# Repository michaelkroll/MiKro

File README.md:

MiKro
==========

The Arduino UNO form factor based MiKro which is using an ATmega 1284p uC from Atmel
Details see on Michael Kroll's Blog at http://www.mkroll.mobi/?page_id=1696
 
Photos
===

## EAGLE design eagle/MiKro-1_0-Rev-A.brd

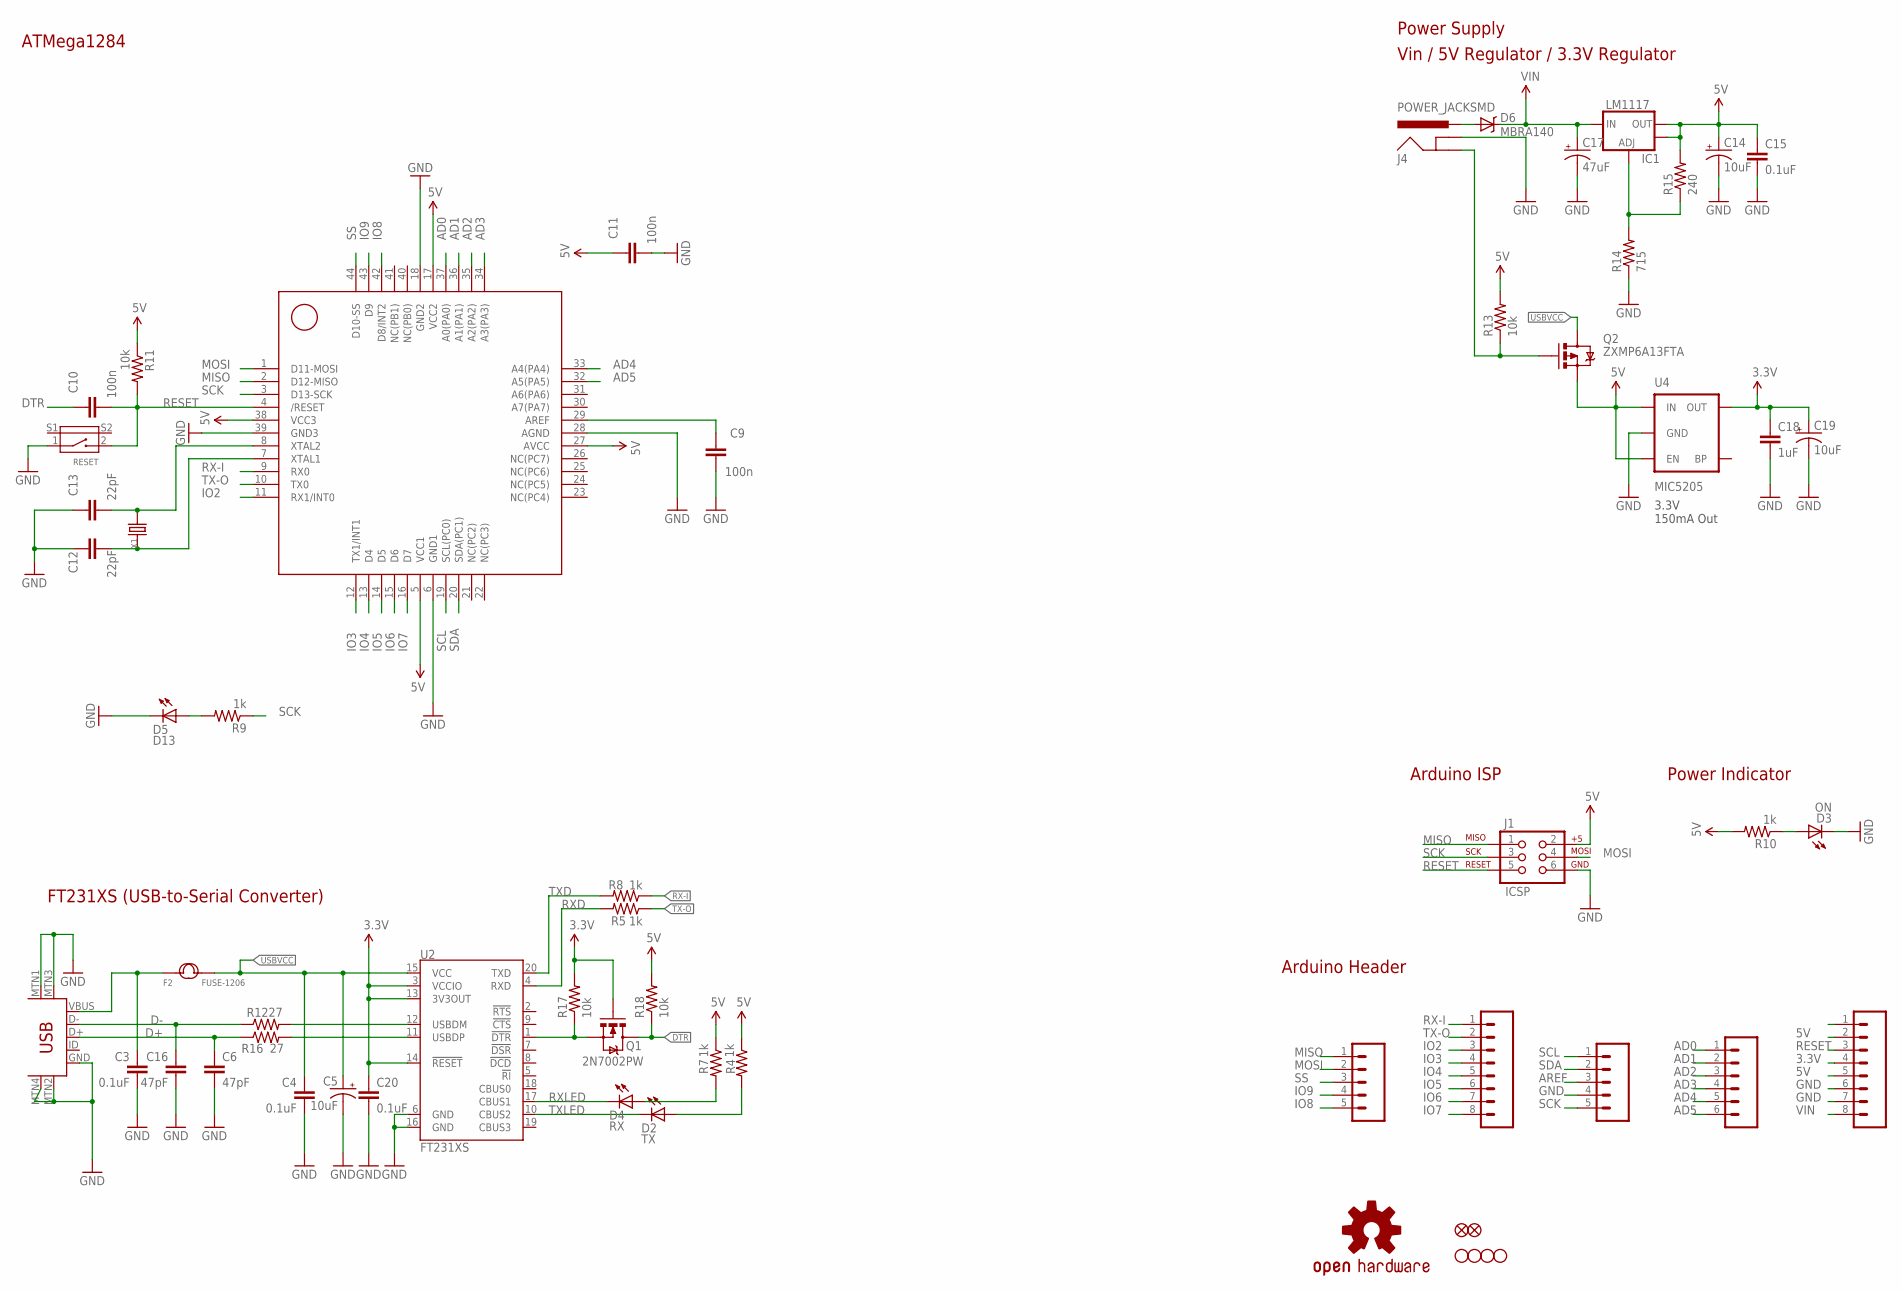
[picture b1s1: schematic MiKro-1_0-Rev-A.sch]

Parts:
C3, C4, C15, C20: 0.1uF; 0603-CAP
C5, C14, C19: 10uF; EIA3216
C6, C16: 47pF; 0603-CAP
C9, C10, C11: 100n; 0603-CAP
C12, C13: 22pF; 0603-CAP
C17: 47uF; PANASONIC_D
C18: 1uF; 0603-CAP
D2: TX; LED-0603
D3: ON; LED-0603
D4: RX; LED-0603
D5: D13; LED-0603
D6: MBRA140; SMA-DIODE
F2: FUSE-1206; F1206
IC1: LM1117; SOT223-ALT1
J1: ICSP; 2X3
J4: POWER_JACKSMD; POWER_JACK_SMD
JP1, JP7: M08LONGPADS; 1X08_LONGPADS
JP3, JP4, JP5, JP6: STAND-OFF
JP8, JP9: FIDUCIAL1X2; FIDUCIAL-1X2
JP11: M06LONGPADS; 1X06_LONGPADS
JP12, JP13: M05PTH_LONGPADS; 1X05_LONGPADS
LOGO1: OSHW-LOGOM; OSHW-LOGO-M
Q1: 2N7002PW; SOT323
Q2: ZXMP6A13FTA; SOT23-3
R4, R5, R7, R8, R9, R10: 1k; 0603-RES
R11, R13, R17, R18: 10k; 0603-RES
R12, R16: 27; 0603-RES
R14: 715; 0603-RES
R15: 240; 0603-RES
RESET: BUTTON-2P-REINFORCE-3100060P1; 4P-SMD-7.0X3.5X3.5H-90D
U2: FT231XS; SSOP20_L
U3: ATMEGA1284P; TQFP44
U4: MIC5205; SOT23-5
U$3: USB-MINIB-5PIN; USB-MINIB
X1: CRYSTAL-0500290P1; 2P-SMD-5.0X3.2

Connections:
3.3V: C18.1, C19.A (+), C20.1, JP7.4, Q1.1 (G), R17.2, U2.3 (VCCIO), U2.13 (3V3OUT), U2.14 (!RESET), U4.5 (OUT)
5V: C11.1, C14.A (+), C15.1, IC1.2 (OUT), IC1.4 (OUT), J1.2, JP7.2, JP7.5, Q2.2 (S), R4.1, R7.1, R10.2, R11.1, R13.2, R15.2, R18.2, U3.5 (VCC1), U3.17 (VCC2), U3.27 (AVCC), U3.38 (VCC3), U4.1 (IN), U4.3 (EN)
AD0: JP11.1, U3.37 (A0(PA0))
AD1: JP11.2, U3.36 (A1(PA1))
AD2: JP11.3, U3.35 (A2(PA2))
AD3: JP11.4, U3.34 (A3(PA3))
AD4: JP11.5, U3.33 (A4(PA4))
AD5: JP11.6, U3.32 (A5(PA5))
AREF: JP12.3
D+: C6.1, R16.1, U$3.D+
D-: C16.1, R12.1, U$3.D-
DTR: C10.1, Q1.3 (D), R18.1
GND: C3.2, C4.2, C5.C (-), C6.2, C9.2, C11.2, C12.1, C13.1, C14.C (-), C15.2, C16.2, C17.-, C18.2, C19.C (-), C20.2, D3.C, D5.C, J1.6, J4.GND (GNDBREAK), JP7.6, JP7.7, JP12.4, R14.1, RESET.1, U2.6 (GND), U2.16 (GND), U3.6 (GND1), U3.18 (GND2), U3.28 (AGND), U3.39 (GND3), U4.2 (GND), U$3.GND, U$3.MTN1 (MTN2), U$3.MTN2 (MTN3), U$3.MTN3 (MTN1), U$3.MTN4
INSERT: J4.P$4 (GND), Q2.1 (G), R13.1
IO2: JP1.3, U3.11 (RX1/INT0)
IO3: JP1.4, U3.12 (TX1/INT1)
IO4: JP1.5, U3.13 (D4)
IO5: JP1.6, U3.14 (D5)
IO6: JP1.7, U3.15 (D6)
IO7: JP1.8, U3.16 (D7)
IO8: JP13.5, U3.42 (D8/INT2)
IO9: JP13.4, U3.43 (D9)
MISO: J1.1, JP13.1, U3.2 (D12-MISO)
MOSI: J1.4, JP13.2, U3.1 (D11-MOSI)
unnamed: D3.A, R10.1
unnamed: D5.A, R9.2
unnamed: C13.2, U3.8 (XTAL2), X1.2
unnamed: D2.A, R4.2
unnamed: C12.2, U3.7 (XTAL1), X1.1
unnamed: C9.1, U3.29 (AREF)
unnamed: D4.A, R7.2
unnamed: IC1.1 (ADJ), R14.2, R15.1
unnamed: R12.2, U2.12 (USBDM)
unnamed: R16.2, U2.11 (USBDP)
unnamed: Q1.2 (S), R17.1, U2.1 (!DTR)
PWRIN1: D6.A, J4.VIN0 (PWR)
RESET: C10.2, J1.5, JP7.3, R11.2, RESET.2, U3.4 (/RESET)
RX-I: JP1.1, R8.1, U3.9 (RX0)
RXD: R5.2, U2.4 (RXD)
RXLED: D4.C, U2.17 (CBUS1)
SCK: J1.3, JP12.5, R9.1, U3.3 (D13-SCK)
SCL: JP12.1, U3.19 (SCL(PC0))
SDA: JP12.2, U3.20 (SDA(PC1))
SS: JP13.3, U3.44 (D10-SS)
TX-O: JP1.2, R5.1, U3.10 (TX0)
TXD: R8.2, U2.20 (TXD)
TXLED: D2.C, U2.10 (CBUS2)
USBVCC: C4.1, C5.A (+), F2.2, Q2.3 (D), U2.15 (VCC)
VIN: C17.+, D6.C, IC1.3 (IN), JP7.8
VUSB: C3.1, F2.1, U$3.VBUS

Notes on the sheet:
Vin / 5V Regulator / 3.3V Regulator
Arduino ISP
Arduino Header
Power Indicator
ATMega1284
Power Supply
3.3V 150mA Out
FT231XS (USB-to-Serial Converter)

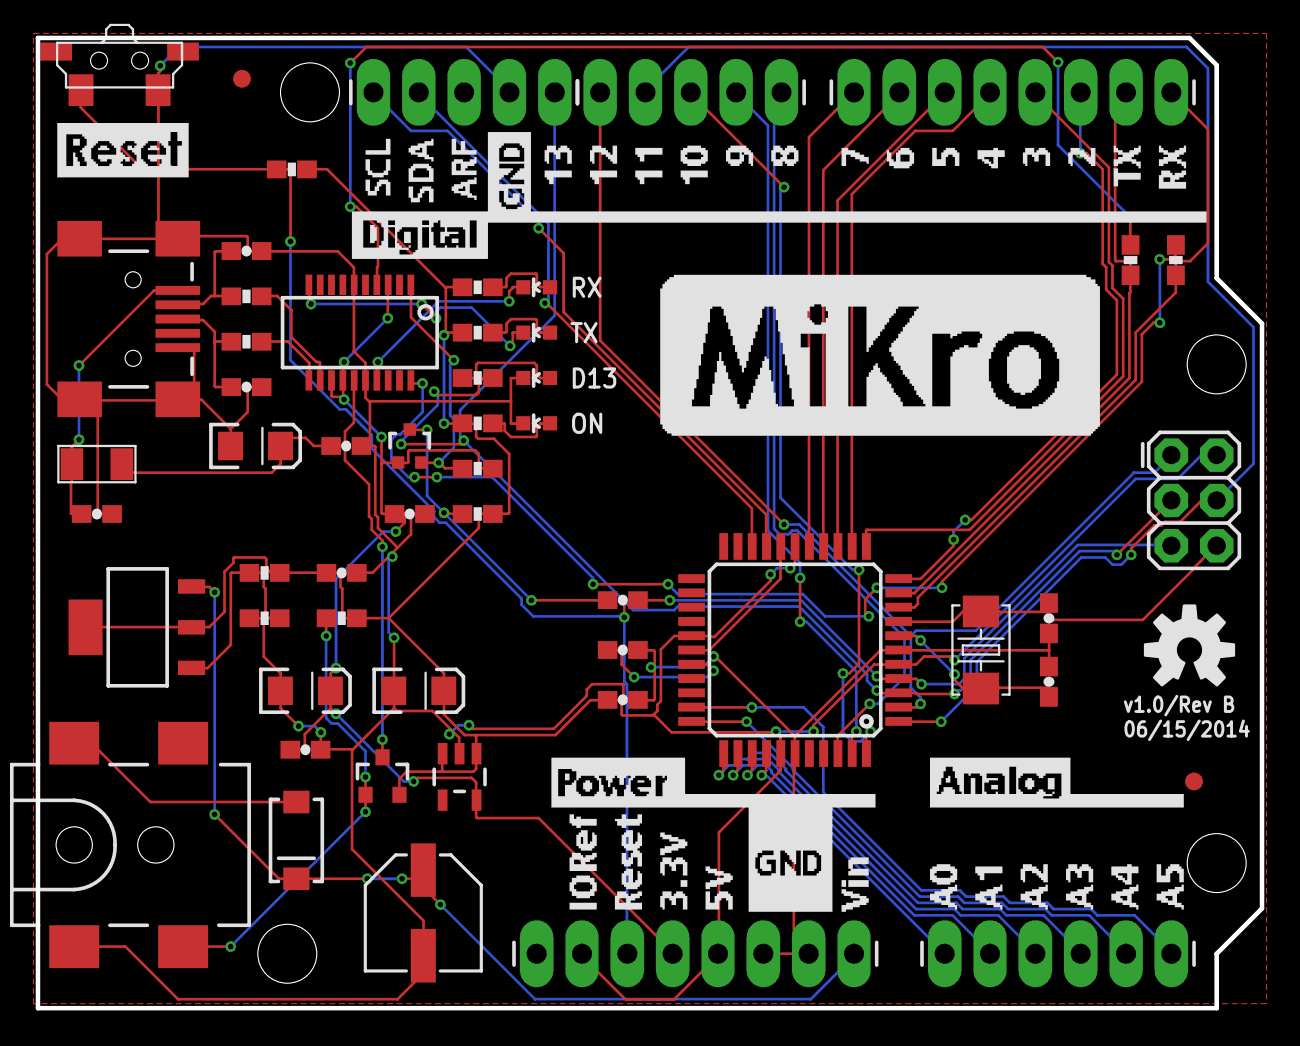
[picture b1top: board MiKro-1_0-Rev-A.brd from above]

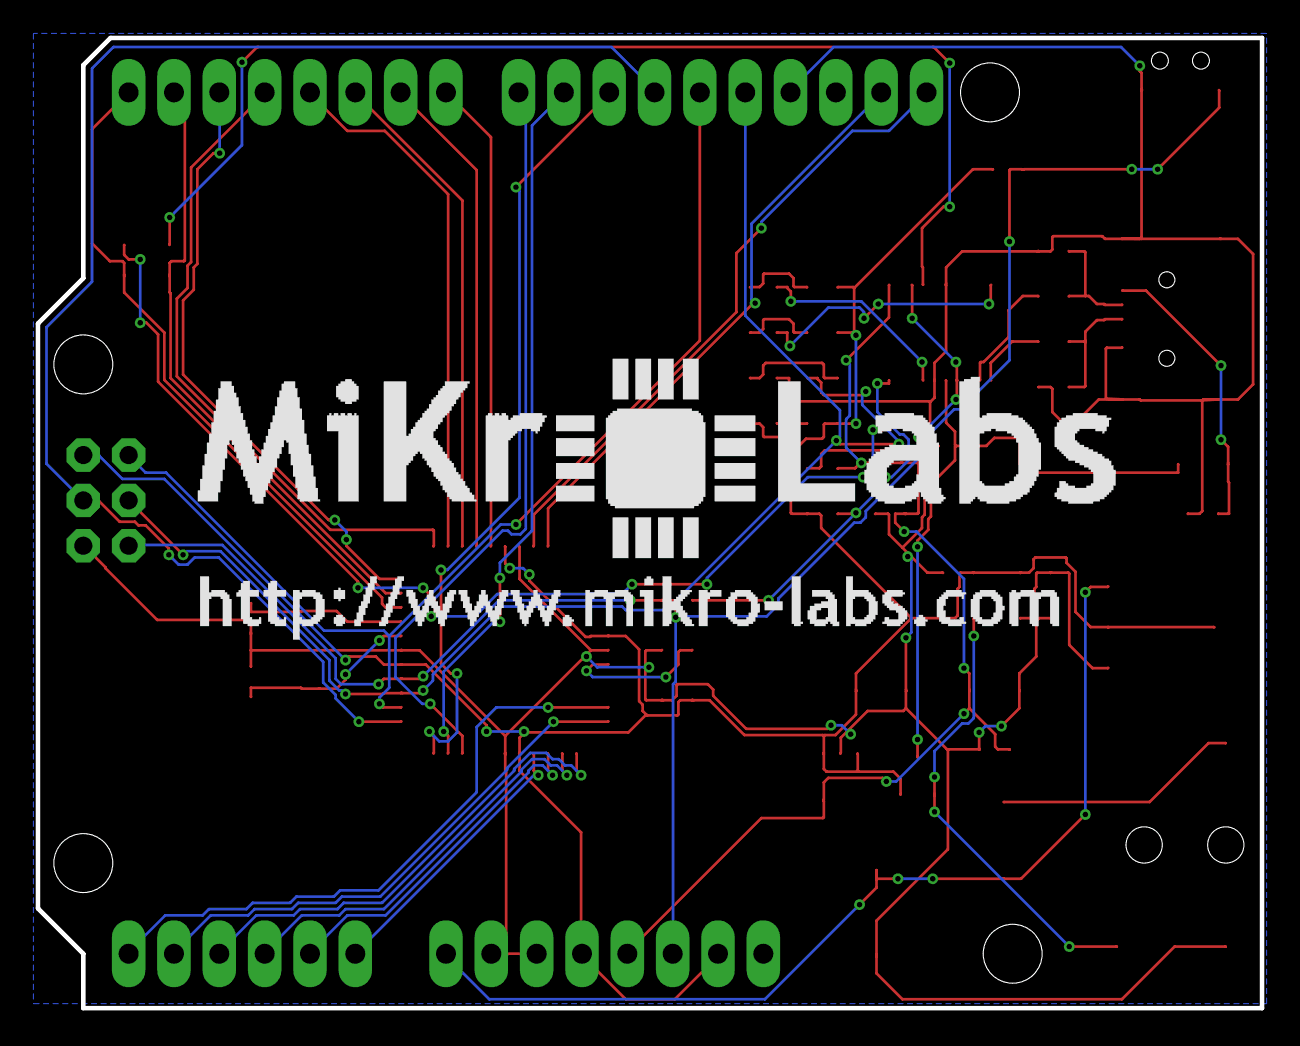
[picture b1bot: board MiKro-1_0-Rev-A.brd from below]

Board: 4 copper layers, 68.6 x 54.4 mm, 65 parts (2 on the bottom side), 49 nets.

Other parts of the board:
U$16: POWER-ANALOG
U$17: DIGITAL
U$19: MIKROLABS-LOGO-LARGE
U$20: MIKROLABS-URL
U$21: RESET
U$22: MIKRO

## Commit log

2014-06-28 Initial commit of the Work in Progress (WIP) MiKro.

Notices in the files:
parts and their libraries:
SparkFun-Connectors: Licensing: CC v3.0 Share-Alike You are welcome to use this library for commercial purposes.
